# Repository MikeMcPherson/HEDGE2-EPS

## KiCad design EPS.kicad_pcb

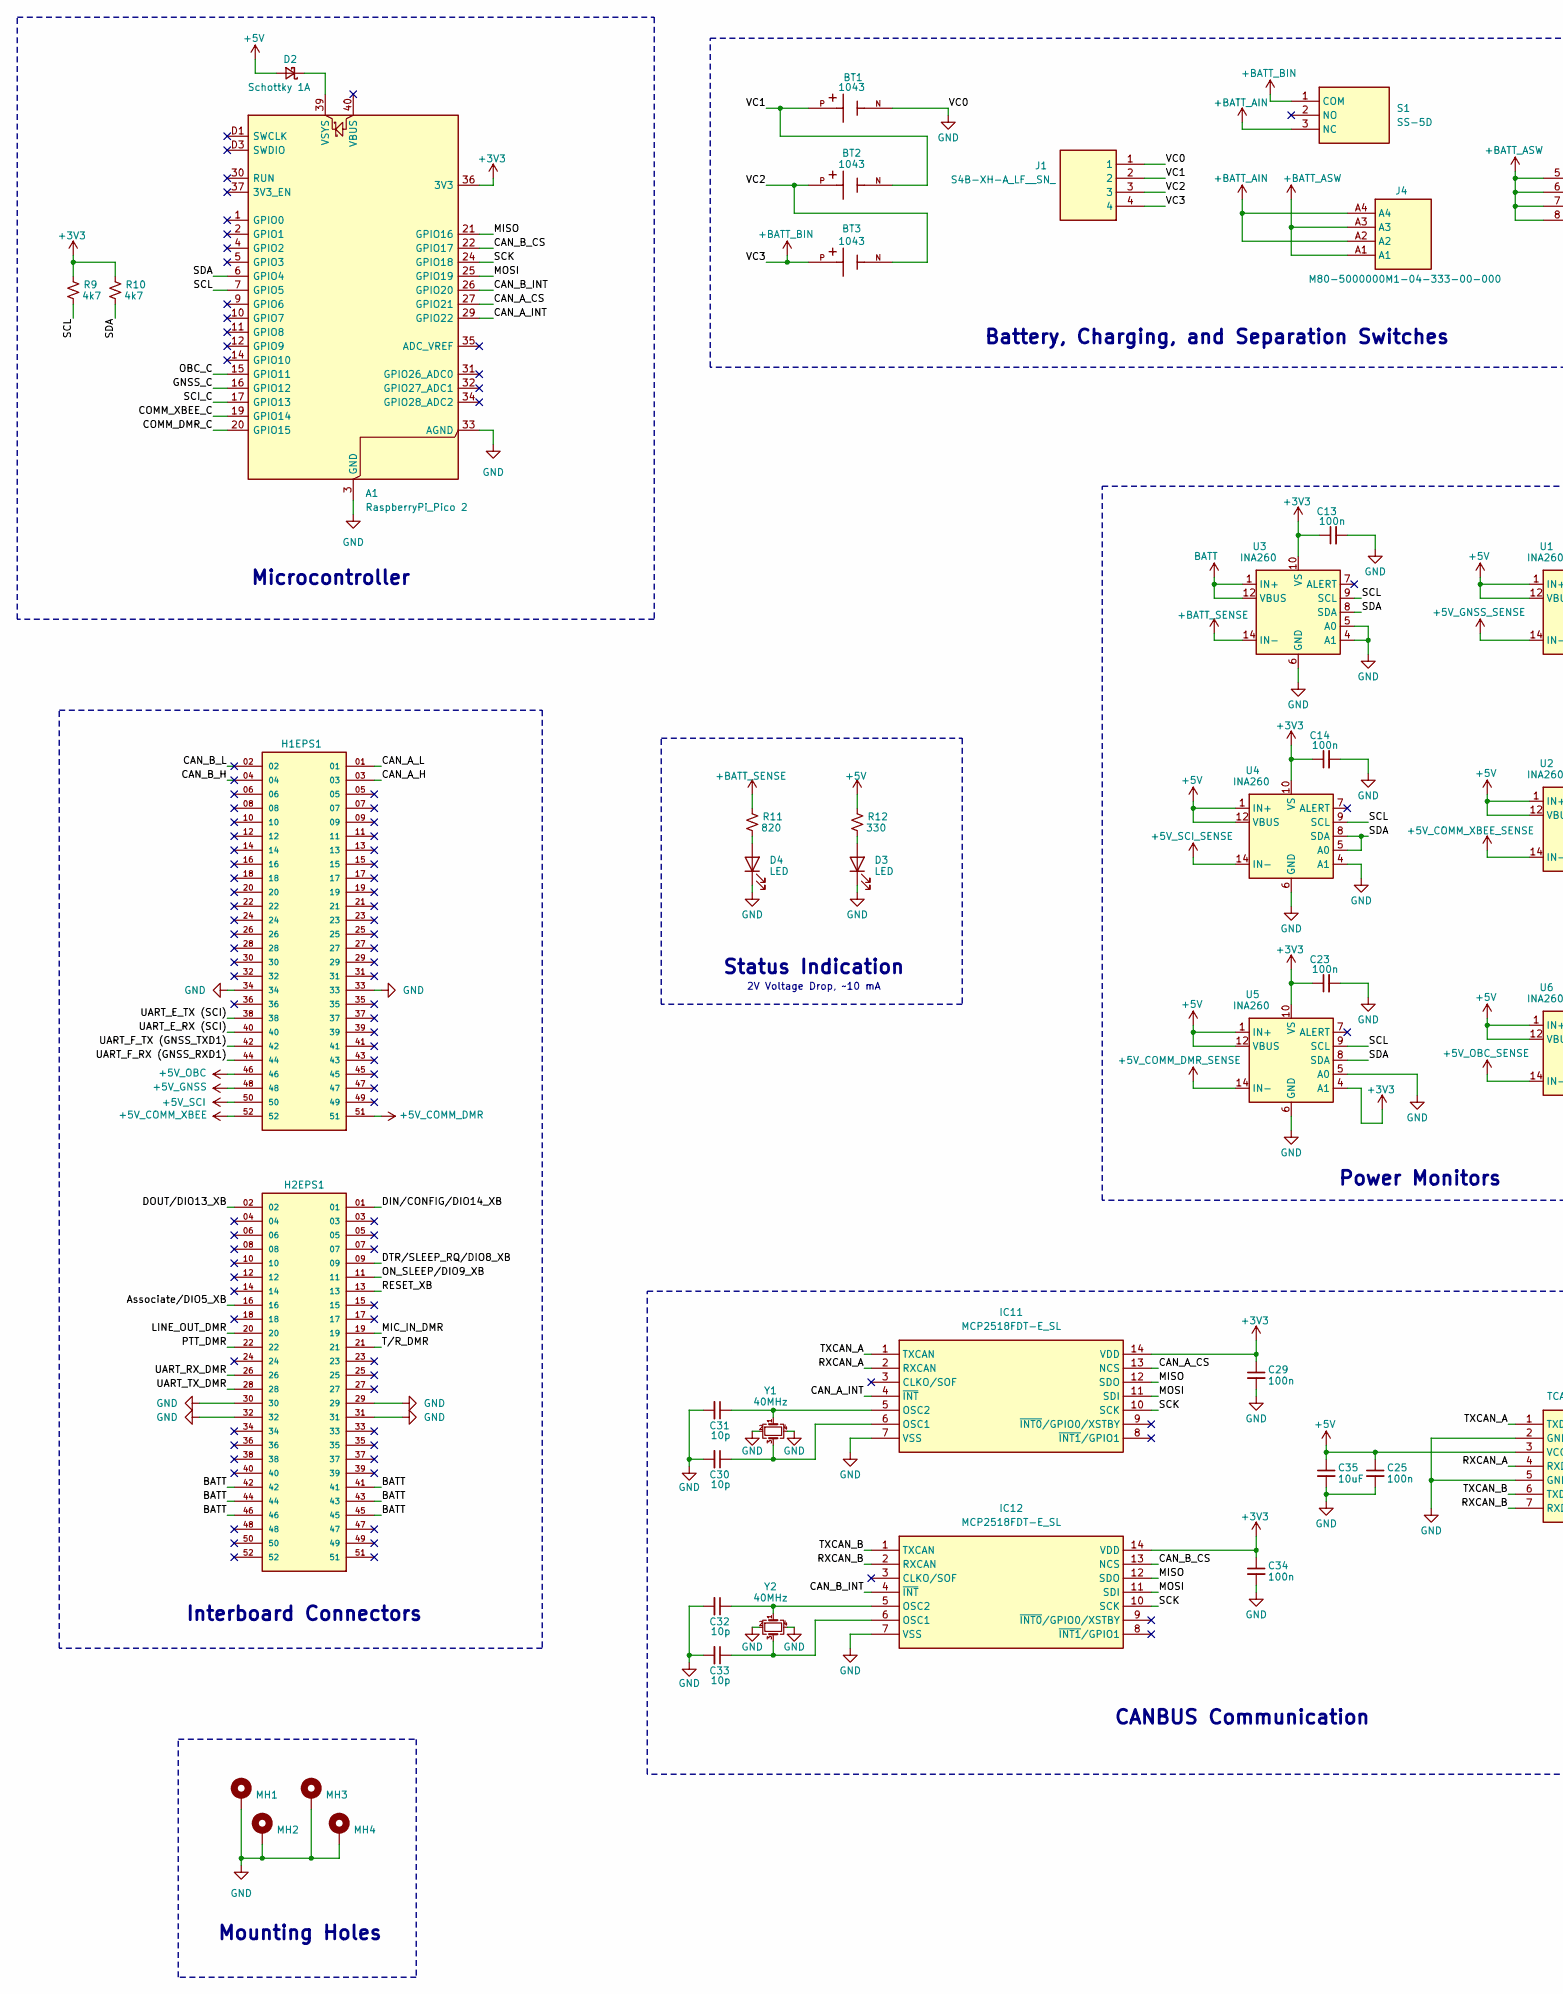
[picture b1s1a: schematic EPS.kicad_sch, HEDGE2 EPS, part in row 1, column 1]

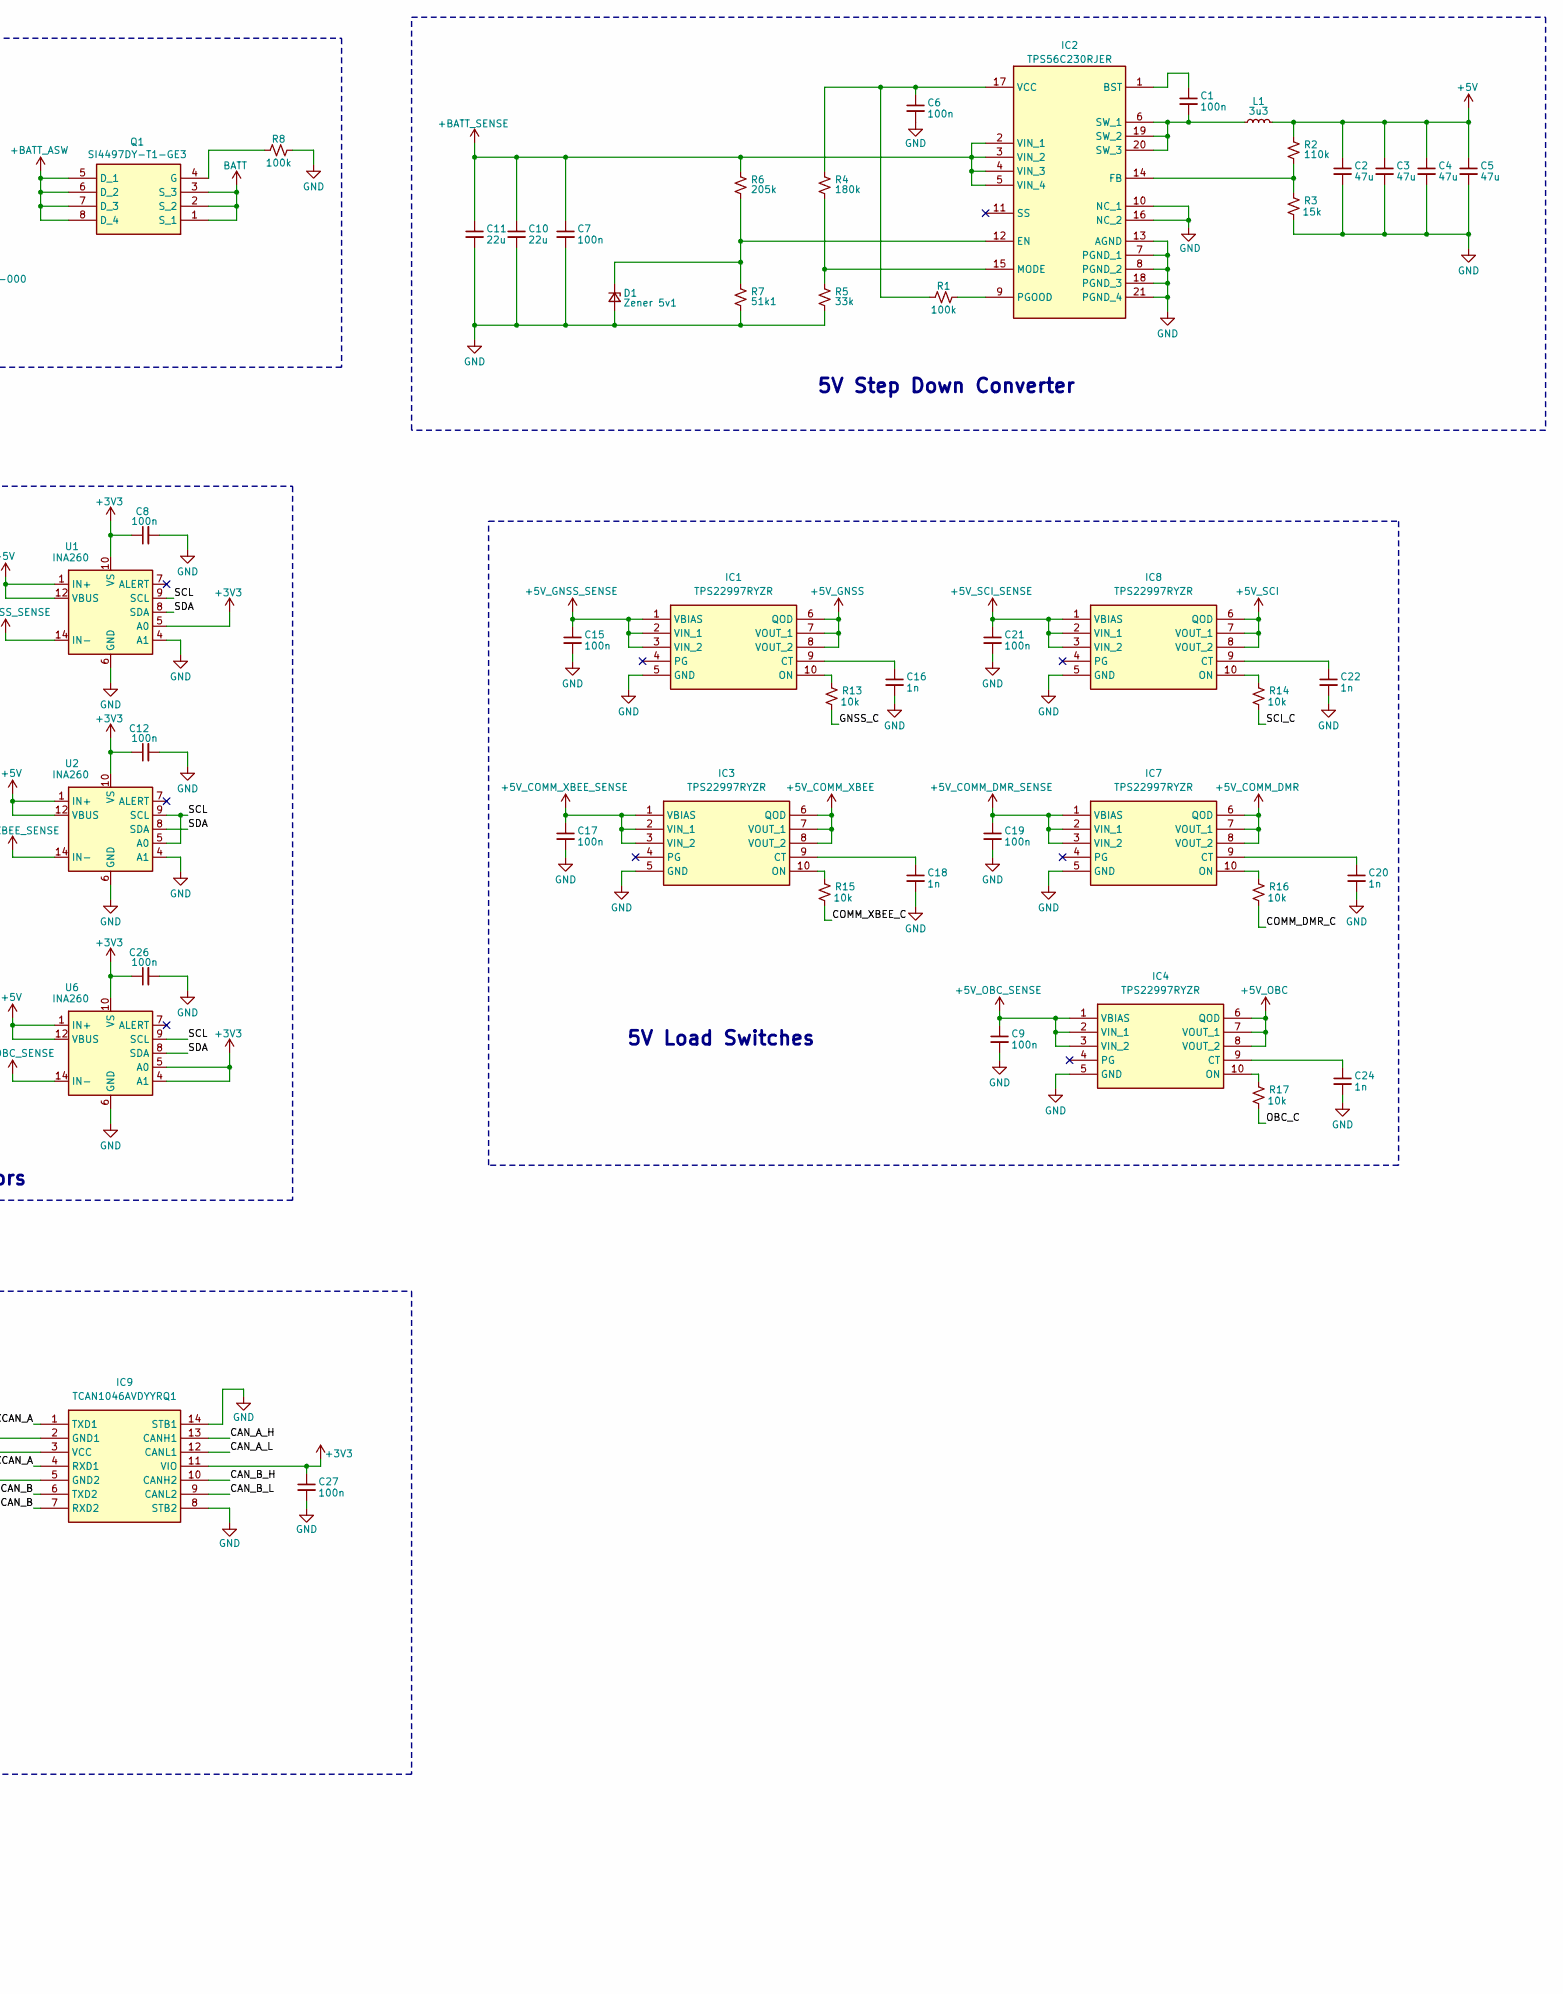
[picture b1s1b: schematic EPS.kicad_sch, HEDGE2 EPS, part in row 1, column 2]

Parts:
A1: RaspberryPi_Pico 2; RaspberryPi_Pico_SMD_HandSolder; DigiKey Part Number 2648-SC1631CT-ND
BT1, BT2, BT3: 1043; BAT_1043; PARTREV J; DigiKey Part Number 36-1043-ND
C1, C6, C7, C8, C9, C12, C13, C14, C15, C17, C19, C21, C23, C25, C26, C27, C29, C34: 100n; C_0603_1608Metric
C2, C3, C4, C5: 47u; C_1206_3216Metric
C10, C11: 22u; C_1206_3216Metric
C16, C18, C20, C22, C24: 1n; C_0603_1608Metric
C30, C31, C32, C33: 10p; C_0603_1608Metric
C35: 10uF; C_0603_1608Metric
D1: Zener 5v1; D_SOD-123; DigiKey Part Number MMSZ5231B-FDICT-ND
D2: Schottky 1A; D_SOD-123; DigiKey Part Number MBR130LSFT1GOSCT-ND
D3, D4: LED; LED_D3.0mm; DigiKey Part Number 732-5005-ND
H1EPS1, H2EPS1: Conn_02x26_Odd_Even; SAMTEC_ESQ-126-39-G-D; Manufacturer_Part_Number ESQ-126-39-G-D; Mouser Part Number 200-ESQ12639GD
IC1, IC3, IC4, IC7, IC8: TPS22997RYZR; Manufacturer_Part_Number TPS22997RYZR; Mouser Part Number 595-TPS22997RYZR
IC2: TPS56C230RJER; Manufacturer_Part_Number TPS56C230RJER; Mouser Part Number 595-TPS56C230RJER
IC9: TCAN1046AVDYYRQ1; Manufacturer_Part_Number TCAN1046AVDYYRQ1; Mouser Part Number 595-TCAN1046AVDYYRQ1
IC11, IC12: MCP2518FDT-E_SL; Manufacturer_Part_Number MCP2518FDT-E/SL; Mouser Part Number 579-MCP2518FDT-E/SL
J1: S4B-XH-A_LF__SN_; S4BXHALFSN; Manufacturer_Part_Number S4B-XH-A(LF)(SN); Mouser Part Number N/A
J4: M80-5000000M1-04-333-00-000; M805000000M10433300000; Manufacturer_Part_Number M80-5000000M1-04-333-00-000; Mouser Part Number 855-0000M10433300000
L1: 3u3; 744393465033; DigiKey Part Number 732-744393465033CT-ND
MH1, MH2, MH3, MH4: MountingHole_Pad; MountingHole_3.2mm_M3_Pad_Via; DigiKey Part Number NA
Q1: SI4497DY-T1-GE3; Manufacturer_Part_Number SI4497DY-T1-GE3; Mouser Part Number 781-SI4497DY-T1-GE3
R1, R8: 100k; R_0603_1608Metric
R2: 110k; R_0603_1608Metric
R3: 15k; R_0603_1608Metric
R4: 180k; R_0603_1608Metric
R5: 33k; R_0603_1608Metric
R6: 205k; R_0603_1608Metric
R7: 51k1; R_0603_1608Metric
R9, R10: 4k7; R_0603_1608Metric
R11: 820; R_0805_2012Metric
R12: 330; R_0805_2012Metric
R13, R14, R15, R16, R17: 10k; R_0603_1608Metric
S1: SS-5D; SS5D; Manufacturer_Part_Number SS-5D; Mouser Part Number 653-SS-5D
U1, U2, U3, U4, U5, U6: INA260; TSSOP-16_4.4x5mm_P0.65mm; DigiKey Part Number 296-47777-1-ND
Y1, Y2: 40MHz; ABM10AIG-40.000MHZ-7-J1Z-T; DigiKey Part Number 535-15281-1-ND

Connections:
+3V3: A1.36 (3V3), C8.1, C12.1, C13.1, C14.1, C23.1, C26.1, C27.1, C29.1, C34.1, IC9.11 (VIO), IC11.14 (VDD), IC12.14 (VDD), R9.1, R10.1, U1.5 (A0), U1.10 (VS), U2.10 (VS), U3.10 (VS), U4.10 (VS), U5.4 (A1), U5.10 (VS), U6.4 (A1), U6.5 (A0), U6.10 (VS)
+5V: C2.1, C3.1, C4.1, C5.1, C25.1, C35.1, D2.2 (A), IC9.3 (VCC), L1.2, R2.1, R12.1, U1.1 (IN+), U1.2 (IN+), U1.3 (IN+), U1.12 (VBUS), U2.1 (IN+), U2.2 (IN+), U2.3 (IN+), U2.12 (VBUS), U4.1 (IN+), U4.2 (IN+), U4.3 (IN+), U4.12 (VBUS), U5.1 (IN+), U5.2 (IN+), U5.3 (IN+), U5.12 (VBUS), U6.1 (IN+), U6.2 (IN+), U6.3 (IN+), U6.12 (VBUS)
+5V_COMM_DMR: H1EPS1.51, IC7.6 (QOD), IC7.7 (VOUT_1), IC7.8 (VOUT_2)
+5V_COMM_DMR_SENSE: C19.1, IC7.1 (VBIAS), IC7.2 (VIN_1), IC7.3 (VIN_2), U5.14 (IN-), U5.15 (IN-), U5.16 (IN-)
+5V_COMM_XBEE: H1EPS1.52, IC3.6 (QOD), IC3.7 (VOUT_1), IC3.8 (VOUT_2)
+5V_COMM_XBEE_SENSE: C17.1, IC3.1 (VBIAS), IC3.2 (VIN_1), IC3.3 (VIN_2), U2.14 (IN-), U2.15 (IN-), U2.16 (IN-)
+5V_GNSS: H1EPS1.48, IC1.6 (QOD), IC1.7 (VOUT_1), IC1.8 (VOUT_2)
+5V_GNSS_SENSE: C15.1, IC1.1 (VBIAS), IC1.2 (VIN_1), IC1.3 (VIN_2), U1.14 (IN-), U1.15 (IN-), U1.16 (IN-)
+5V_OBC: H1EPS1.46, IC4.6 (QOD), IC4.7 (VOUT_1), IC4.8 (VOUT_2)
+5V_OBC_SENSE: C9.1, IC4.1 (VBIAS), IC4.2 (VIN_1), IC4.3 (VIN_2), U6.14 (IN-), U6.15 (IN-), U6.16 (IN-)
+5V_SCI: H1EPS1.50, IC8.6 (QOD), IC8.7 (VOUT_1), IC8.8 (VOUT_2)
+5V_SCI_SENSE: C21.1, IC8.1 (VBIAS), IC8.2 (VIN_1), IC8.3 (VIN_2), U4.14 (IN-), U4.15 (IN-), U4.16 (IN-)
+BATT_AIN: J4.A2, J4.A4, S1.3 (NC)
+BATT_ASW: J4.A1, J4.A3, Q1.5 (D_1), Q1.6 (D_2), Q1.7 (D_3), Q1.8 (D_4)
+BATT_BIN: BT3.P, J1.4, S1.1 (COM)
+BATT_SENSE: C7.1, C10.1, C11.1, IC2.2 (VIN_1), IC2.3 (VIN_2), IC2.4 (VIN_3), IC2.5 (VIN_4), R6.1, R11.1, U3.14 (IN-), U3.15 (IN-), U3.16 (IN-)
/Associate/DIO5_XB: H2EPS1.16
/CAN_A_CS: A1.27 (GPIO21), IC11.13 (NCS)
/CAN_A_H: H1EPS1.03, IC9.13 (CANH1)
/CAN_A_INT: A1.29 (GPIO22), IC11.4 (~INT)
/CAN_A_L: H1EPS1.01, IC9.12 (CANL1)
/CAN_B_CS: A1.22 (GPIO17), IC12.13 (NCS)
/CAN_B_H: H1EPS1.04, IC9.10 (CANH2)
/CAN_B_INT: A1.26 (GPIO20), IC12.4 (~INT)
/CAN_B_L: H1EPS1.02, IC9.9 (CANL2)
/COMM_DMR_C: A1.20 (GPIO15), R16.2
/COMM_XBEE_C: A1.19 (GPIO14), R15.2
/DIN/CONFIG/DIO14_XB: H2EPS1.01
/DOUT/DIO13_XB: H2EPS1.02
/DTR/SLEEP_RQ/DIO8_XB: H2EPS1.09
/GNSS_C: A1.16 (GPIO12), R13.2
/LINE_OUT_DMR: H2EPS1.20
/MIC_IN_DMR: H2EPS1.19
/MISO: A1.21 (GPIO16), IC11.12 (SDO), IC12.12 (SDO)
/MOSI: A1.25 (GPIO19), IC11.11 (SDI), IC12.11 (SDI)
/OBC_C: A1.15 (GPIO11), R17.2
/ON_SLEEP/DIO9_XB: H2EPS1.11
/PTT_DMR: H2EPS1.22
/RESET_XB: H2EPS1.13
/RXCAN_A: IC9.4 (RXD1), IC11.2 (RXCAN)
/RXCAN_B: IC9.7 (RXD2), IC12.2 (RXCAN)
/SCI_C: A1.17 (GPIO13), R14.2
/SCK: A1.24 (GPIO18), IC11.10 (SCK), IC12.10 (SCK)
/SCL: A1.7 (GPIO5), R9.2, U1.9 (SCL), U2.5 (A0), U2.9 (SCL), U3.9 (SCL), U4.9 (SCL), U5.9 (SCL), U6.9 (SCL)
/SDA: A1.6 (GPIO4), R10.2, U1.8 (SDA), U2.8 (SDA), U3.8 (SDA), U4.5 (A0), U4.8 (SDA), U5.8 (SDA), U6.8 (SDA)
/TXCAN_A: IC9.1 (TXD1), IC11.1 (TXCAN)
/TXCAN_B: IC9.6 (TXD2), IC12.1 (TXCAN)
/T/R_DMR: H2EPS1.21
/UART_E_RX (SCI): H1EPS1.40
/UART_E_TX (SCI): H1EPS1.38
/UART_F_RX (GNSS_RXD1): H1EPS1.44
/UART_F_TX (GNSS_TXD1): H1EPS1.42
/UART_RX_DMR: H2EPS1.26
/UART_TX_DMR: H2EPS1.28
/VC1: BT1.P, BT2.N, J1.2
/VC2: BT2.P, BT3.N, J1.3
BATT: H2EPS1.41, H2EPS1.42, H2EPS1.43, H2EPS1.44, H2EPS1.45, H2EPS1.46, Q1.1 (S_1), Q1.2 (S_2), Q1.3 (S_3), U3.1 (IN+), U3.2 (IN+), U3.3 (IN+), U3.12 (VBUS)
GND: A1.3 (GND), A1.8 (GND), A1.13 (GND), A1.18 (GND), A1.23 (GND), A1.28 (GND), A1.33 (AGND), A1.38 (GND), A1.D2 (GND), BT1.N, C2.2, C3.2, C4.2, C5.2, C6.2, C7.2, C8.2, C9.2, C10.2, C11.2, C12.2, C13.2, C14.2, C15.2, C16.2, C17.2, C18.2, C19.2, C20.2, C21.2, C22.2, C23.2, C24.2, C25.2, C26.2, C27.2, C29.2, C30.2, C31.2, C32.2, C33.2, C34.2, C35.2, D1.2 (A), D3.1 (K), D4.1 (K), H1EPS1.33, H1EPS1.34, H2EPS1.29, H2EPS1.30, H2EPS1.31, H2EPS1.32, IC1.5 (GND), IC2.7 (PGND_1), IC2.8 (PGND_2), IC2.10 (NC_1), IC2.13 (AGND), IC2.16 (NC_2), IC2.18 (PGND_3), IC2.21 (PGND_4), IC3.5 (GND), IC4.5 (GND), IC7.5 (GND), IC8.5 (GND), IC9.2 (GND1), IC9.5 (GND2), IC9.8 (STB2), IC9.14 (STB1), IC11.7 (VSS), IC12.7 (VSS), J1.1, MH1.1, MH2.1, MH3.1, MH4.1, R3.2, R5.2, R7.2, R8.1, U1.4 (A1), U1.6 (GND), U1.11 (GND), U2.4 (A1), U2.6 (GND), U2.11 (GND), U3.4 (A1), U3.5 (A0), U3.6 (GND), U3.11 (GND), U4.4 (A1), U4.6 (GND), U4.11 (GND), U5.5 (A0), U5.6 (GND), U5.11 (GND), U6.6 (GND), U6.11 (GND), Y1.2, Y1.4, Y2.2, Y2.4
unnamed: A1.39 (VSYS), D2.1 (K)
unnamed: D1.1 (K), IC2.12 (EN), R6.2, R7.1
unnamed: D3.2 (A), R12.2
unnamed: D4.2 (A), R11.2
unnamed: C16.1, IC1.9 (CT)
unnamed: IC1.10 (ON), R13.1
unnamed: C1.1, IC2.1 (BST)
unnamed: IC2.14 (FB), R2.2, R3.1
unnamed: IC2.15 (MODE), R4.2, R5.1
unnamed: IC2.9 (PGOOD), R1.1
unnamed: C1.2, IC2.6 (SW_1), IC2.19 (SW_2), IC2.20 (SW_3), L1.1
unnamed: C6.1, IC2.17 (VCC), R1.2, R4.1
unnamed: C18.1, IC3.9 (CT)
unnamed: IC3.10 (ON), R15.1
unnamed: C24.1, IC4.9 (CT)
unnamed: IC4.10 (ON), R17.1
unnamed: C20.1, IC7.9 (CT)
unnamed: IC7.10 (ON), R16.1
unnamed: C22.1, IC8.9 (CT)
unnamed: IC8.10 (ON), R14.1
unnamed: C30.1, IC11.6 (OSC1), Y1.3
unnamed: C31.1, IC11.5 (OSC2), Y1.1
unnamed: C33.1, IC12.6 (OSC1), Y2.3
unnamed: C32.1, IC12.5 (OSC2), Y2.1
unnamed: Q1.4 (G), R8.2

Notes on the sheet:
Microcontroller
5V Load Switches
Mounting Holes
Interboard Connectors
Power Monitors
CANBUS Communication
2V Voltage Drop, ~10 mA
5V Step Down Converter
Status Indication
Battery, Charging, and Separation Switches

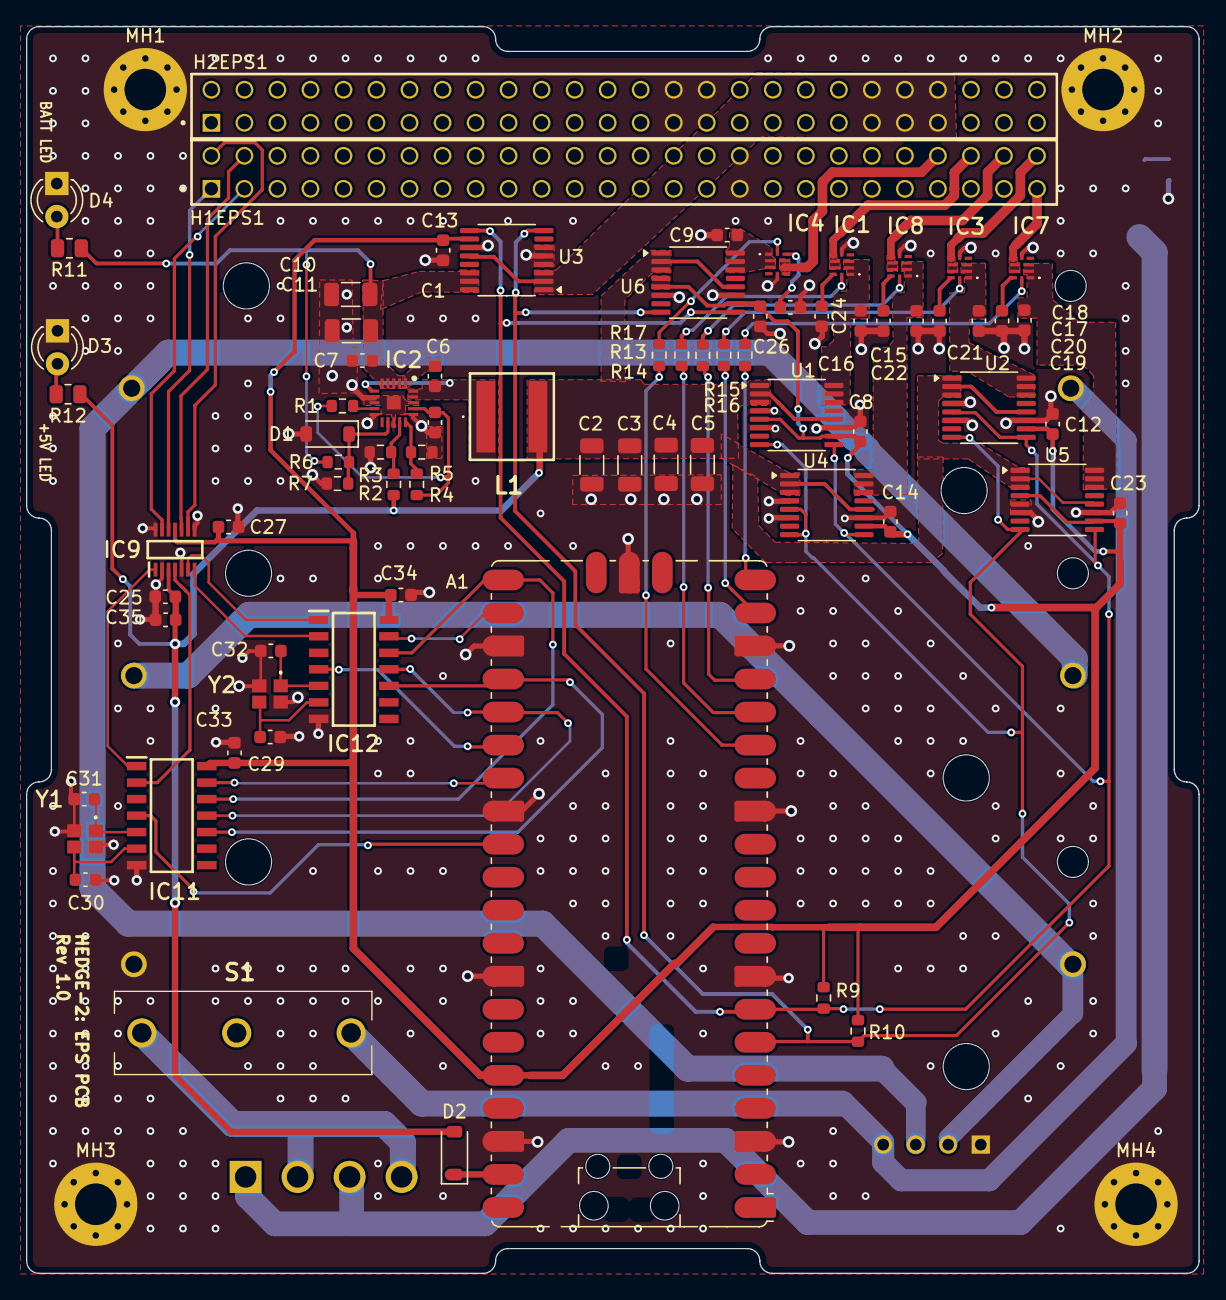
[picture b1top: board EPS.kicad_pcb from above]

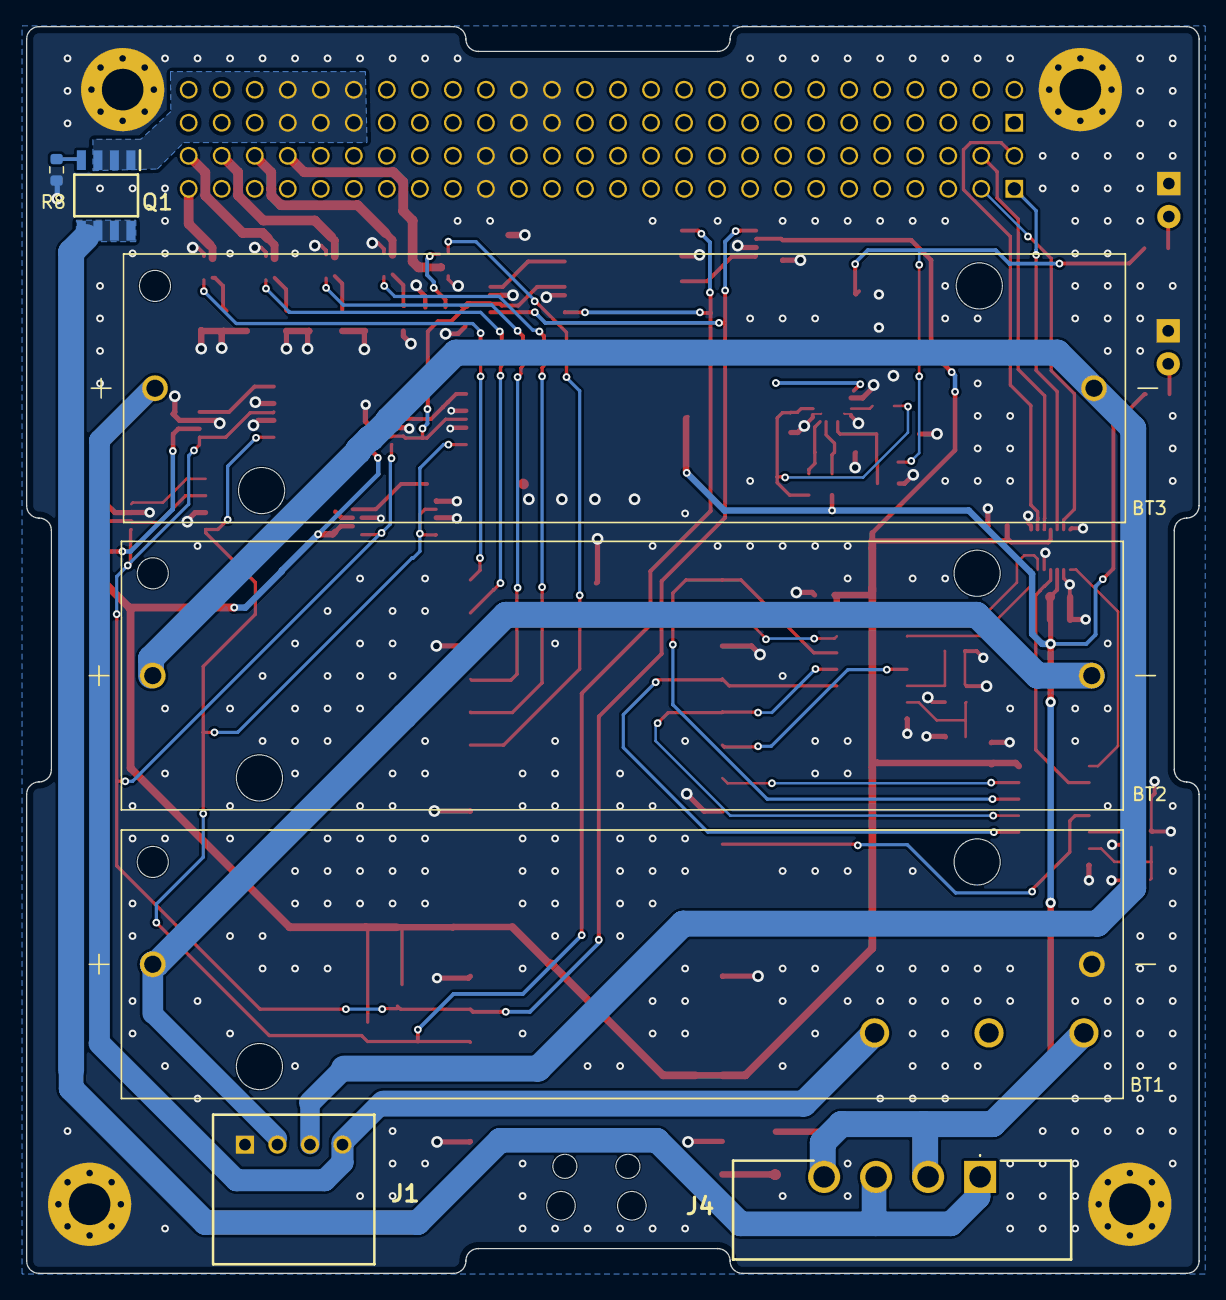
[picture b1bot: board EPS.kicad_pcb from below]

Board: 4 copper layers, 90.2 x 95.9 mm, 87 parts (7 on the bottom side), 67 nets.

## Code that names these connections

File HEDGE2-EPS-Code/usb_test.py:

"""
Sabre III EPS - Phase 1 Diagnostic (Logic & USB Power Only)
Tests 3.3V rail, I2C comms, and GPIO routing without Main Battery.
"""

from machine import Pin, I2C, SPI
import time
import struct

# ==========================================
# 1. HARDWARE PINS (Mapped strictly to GP numbers)
# ==========================================

# I2C0 Bus (INA260 Power Monitors)
I2C_SDA_PIN = 4  # Physical Pin 6
I2C_SCL_PIN = 5  # Physical Pin 7

# INA260 Addresses
# BATT_SENSE       -> 0x40
# GNSS_SENSE       -> 0x41
# SCI_SENSE        -> 0x42
# COMM_XBEE_SENSE  -> 0x43
# COMM_DMR_SENSE   -> 0x44
# OBC_SENSE        -> 0x45

# SPI0 Bus (MCP2518 CAN Controller)
SPI_MISO_PIN = 16 # Physical Pin 21
SPI_SCK_PIN = 18  # Physical Pin 24
SPI_MOSI_PIN = 19 # Physical Pin 25

# CAN Chip Selects & Interrupts
CAN_B_CS_PIN = 17  # Physical Pin 22
CAN_B_INT_PIN = 20 # Physical Pin 26
CAN_A_CS_PIN = 21  # Physical Pin 27
CAN_A_INT_PIN = 22 # Physical Pin 29

# TPS22997 Load Switch Enable Pins
OBC_C_PIN = 11       # Physical Pin 15
GNSS_C_PIN = 12      # Physical Pin 16
SCI_C_PIN = 13       # Physical Pin 17
COMM_XBEE_C_PIN = 14 # Physical Pin 19
COMM_DMR_C_PIN = 15  # Physical Pin 20

# ==========================================
# 2. INITIALIZATION
# ==========================================

# Setup I2C at 400kHz (Fast Mode) - Block 0 for GP4/GP5
i2c = I2C(0, sda=Pin(I2C_SDA_PIN), scl=Pin(I2C_SCL_PIN), freq=400000)

# Setup SPI (Hardware block 0)
spi = SPI(0, baudrate=1000000, polarity=0, phase=0, 
          sck=Pin(SPI_SCK_PIN), mosi=Pin(SPI_MOSI_PIN), miso=Pin(SPI_MISO_PIN))

# Initialize CS pins high (deselected) so they don't interfere
can_a_cs = Pin(CAN_A_CS_PIN, Pin.OUT, value=1) 
can_b_cs = Pin(CAN_B_CS_PIN, Pin.OUT, value=1) 

# Setup Load Switches (Default OFF)
switches = {
    "OUT_1_OBC": Pin(OBC_C_PIN, Pin.OUT, value=0),
    "OUT_2_GNSS": Pin(GNSS_C_PIN, Pin.OUT, value=0),
    "OUT_3_SCI": Pin(SCI_C_PIN, Pin.OUT, value=0),
    "OUT_4_XBEE": Pin(COMM_XBEE_C_PIN, Pin.OUT, value=0),
    "OUT_5_DMR": Pin(COMM_DMR_C_PIN, Pin.OUT, value=0),
}

# ==========================================
# 3. DIAGNOSTIC TESTS
# ==========================================

def test_ina260_comms():
    print("\n--- TEST 1: I2C BUS & INA260 SCAN ---")
    devices = i2c.scan()
    
    if not devices:
        print("FAIL: No I2C devices found. Check pull-up resistors and 3V3 rail.")
        return
        
    print(f"PASS: Found {len(devices)} device(s) on I2C bus.")
    
    for addr in devices:
        try:
            mfg_id_bytes = i2c.readfrom_mem(addr, 0xFE, 2)
            mfg_id = struct.unpack('>H', mfg_id_bytes)[0]
            
            if mfg_id == 0x5449:
                print(f"  -> Device at {hex(addr)}: Verified INA260 (ID: {hex(mfg_id)})")
            else:
                print(f"  -> Device at {hex(addr)}: Unknown Device (ID: {hex(mfg_id)})")
        except OSError:
            print(f"  -> Device at {hex(addr)}: Unresponsive to ID request.")

# ==========================================
# 4. EXECUTE
# ==========================================

def main():
    print("========================================")
    print("  SABRE III EPS - USB DIAGNOSTIC MODE   ")
    print("========================================")
    
    time.sleep(1) 
    
    test_ina260_comms()
    time.sleep(1)
    
    print("\n========================================")
    print("  DIAGNOSTICS COMPLETE. SYSTEM IDLE.    ")
    print("========================================")

if __name__ == "__main__":
    main()

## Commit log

2025-09-07 Add files
2025-09-07 Change README from HEDGE2-Avionics to HEDGE2-EPS
2025-10-30 Test commit
2025-10-30 updated battery sheet passives values
2025-10-31 Added CAN controller, got rid of one RS485 transceiver
2025-11-06 updates to connectors
2025-11-26 updated the schematic to remove connection to rocksat, linked schmatic symbols to footprints
2025-12-02 began initial layout
2025-12-06 Added most 3d models, continued layout
2025-12-09 Initial layout completed
2026-01-27 Rev 1 version
2026-01-27 Finished routing
2026-01-30 Added sep switch connector and fixes
2026-01-30 Fixed the rest of DRC errors
2026-01-30 cleaned up schematic
2026-02-01 Updated resistor val for reverse pol mosfet
2026-02-04 updated schematic, began revising routing
2026-02-07 implemented updates
2026-02-13 updated bom
2026-04-16 inital code for testing
2026-04-21 update main.py for testing
